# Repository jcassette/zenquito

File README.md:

# Zenquito

Design by J.M. Plantefeve
http://jm.plantefeve.pagesperso-orange.fr

## Class B

R10 = R11 = 68 Ohm

| VDC (V) | Power (W) | Q5       | Q6       | Q7       | Q8       |
| ------- | --------- | -------- | -------- | -------- | -------- |
| 21      | 16        | 2SK1058  | 2SJ162   | none     | none     |
| 25      | 25        | 2SK1058  | 2SJ162   | none     | none     |
| 30      | 40        | 2SK1058  | 2SJ162   | none     | none     |
| 34      | 50        | 2SK1058  | 2SJ162   | 2SK1058  | 2SJ162   |
| 42      | 80        | 2SK1058  | 2SJ162   | 2SK1058  | 2SJ162   |

## Class A

R10 = R11 = 150 Ohm

| VDC (V) | Power (W) | Q5       | Q6       | Q7       | Q8       |
| ------- | --------- | -------- | -------- | -------- | -------- |
| 21      | 16        | 2SK1058  | 2SJ162   | none     | none     |
| 25      | 25        | 2SK1058  | 2SJ162   | 2SK1058  | 2SJ162   |
| 30      | 40        | BUZ900DP | BUZ905DP | BUZ900DP | BUZ905DP |
| 34      | 50        | BUZ900DP | BUZ905DP | BUZ900DP | BUZ905DP |

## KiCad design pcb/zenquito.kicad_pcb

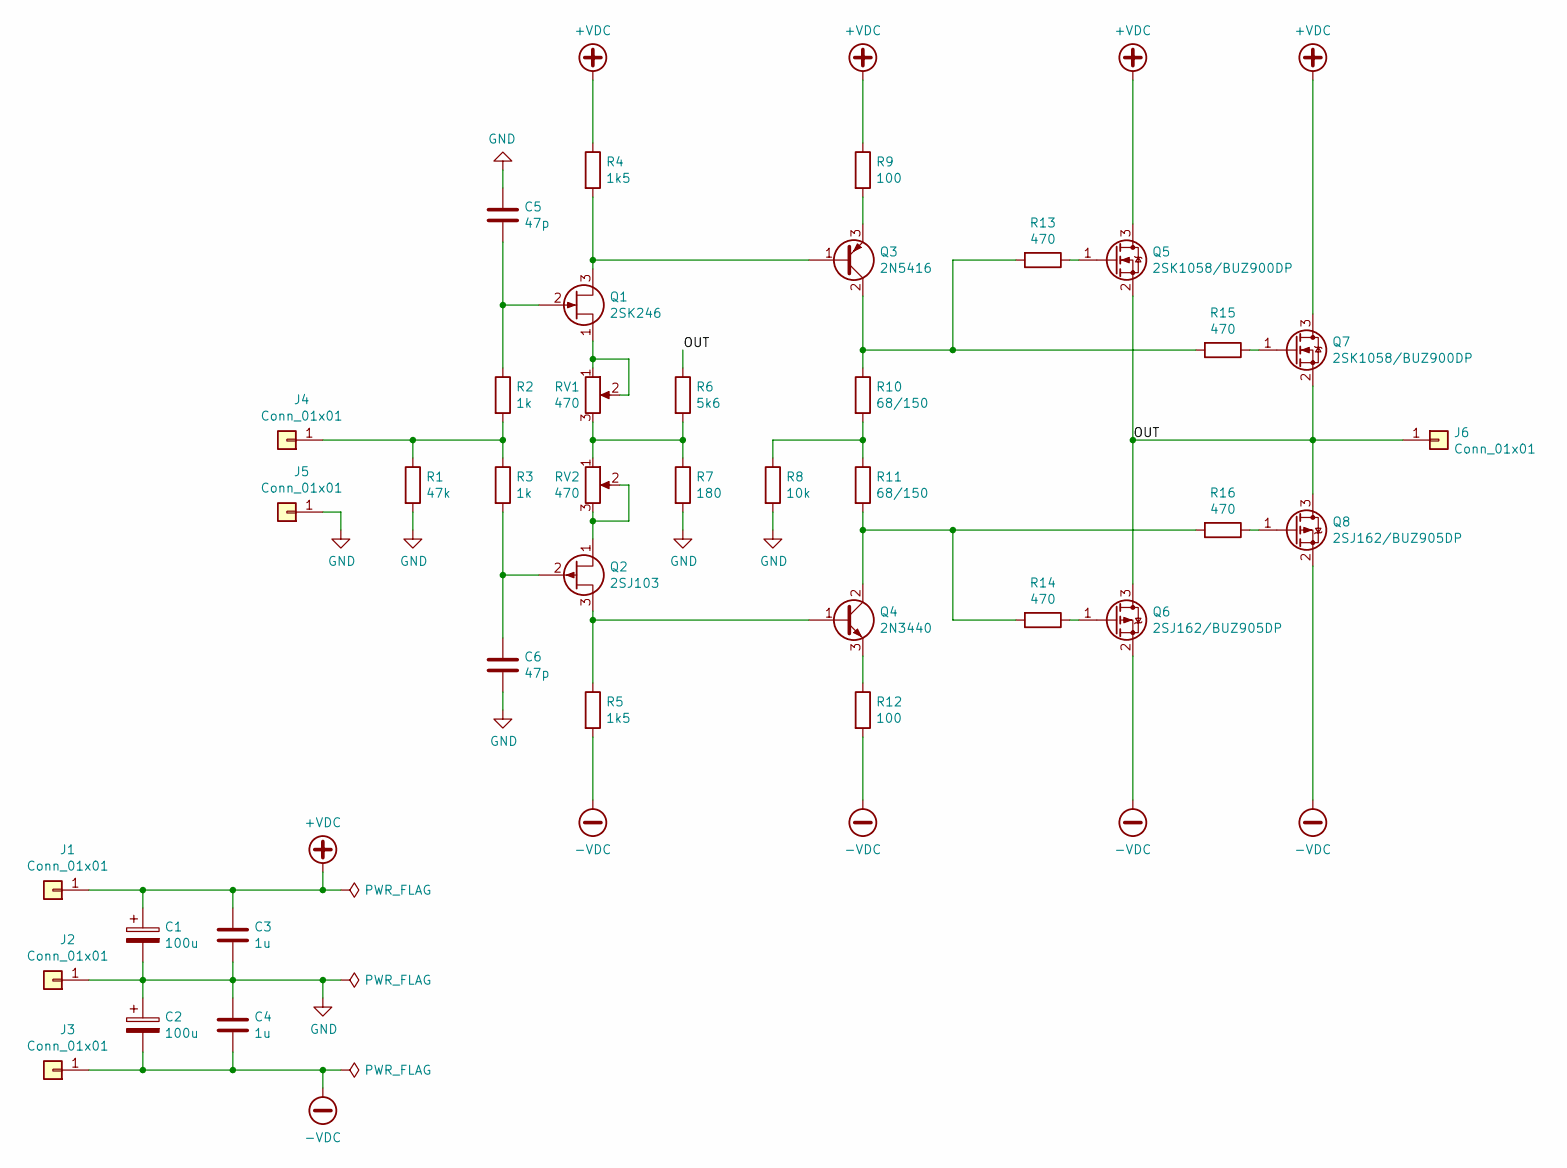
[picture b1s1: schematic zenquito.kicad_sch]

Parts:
C1, C2: 100u; CP_Radial_D8.0mm_P5.00mm
C3, C4: 1u; C_Rect_L7.0mm_W3.5mm_P5.00mm
C5, C6: 47p; C_Rect_L7.0mm_W3.5mm_P5.00mm
J1, J2, J3, J6: Conn_01x01; SolderWire-2.5sqmm_1x01_D2.4mm_OD4.4mm
J4, J5: Conn_01x01; SolderWire-0.5sqmm_1x01_D0.9mm_OD2.1mm
Q1: 2SK246; TO-92_Inline_Wide
Q2: 2SJ103; TO-92_Inline_Wide
Q3: 2N5416; TO-39-3
Q4: 2N3440; TO-39-3
Q5, Q7: 2SK1058/BUZ900DP; TO-3P-3_Vertical
Q6, Q8: 2SJ162/BUZ905DP; TO-3P-3_Vertical
R1: 47k; R_Axial_DIN0411_L9.9mm_D3.6mm_P12.70mm_Horizontal
R2, R3: 1k; R_Axial_DIN0411_L9.9mm_D3.6mm_P12.70mm_Horizontal
R4, R5: 1k5; R_Axial_DIN0411_L9.9mm_D3.6mm_P12.70mm_Horizontal
R6: 5k6; R_Axial_DIN0411_L9.9mm_D3.6mm_P12.70mm_Horizontal
R7: 180; R_Axial_DIN0411_L9.9mm_D3.6mm_P12.70mm_Horizontal
R8: 10k; R_Axial_DIN0411_L9.9mm_D3.6mm_P12.70mm_Horizontal
R9, R12: 100; R_Axial_DIN0411_L9.9mm_D3.6mm_P12.70mm_Horizontal
R10, R11: 68/150; R_Axial_DIN0411_L9.9mm_D3.6mm_P12.70mm_Horizontal
R13, R14, R15, R16: 470; R_Axial_DIN0411_L9.9mm_D3.6mm_P12.70mm_Horizontal
RV1, RV2: 470; Potentiometer_Bourns_3266Y_Vertical

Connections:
+VDC: C1.1, C3.1, J1.1, Q5.3 (D), Q7.3 (D), R4.1, R9.1
-VDC: C2.2, C4.2, J3.1, Q6.2 (S), Q8.2 (S), R5.2, R12.2
/OUT: J6.1, Q5.2 (S), Q6.3 (D), Q7.2 (S), Q8.3 (D), R6.1
GND: C1.2, C2.1, C3.2, C4.1, C5.1, C6.2, J2.1, J5.1, R1.2, R7.2, R8.2
unnamed: C5.2, Q1.2 (G), R2.1
unnamed: C6.1, Q2.2 (G), R3.2
unnamed: J4.1, R1.1, R2.2, R3.1
unnamed: Q1.1 (S), RV1.1, RV1.2
unnamed: Q1.3 (D), Q3.1 (B), R4.2
unnamed: Q2.1 (S), RV2.2, RV2.3
unnamed: Q2.3 (D), Q4.1 (B), R5.1
unnamed: Q3.2 (C), R10.1, R13.2, R15.2
unnamed: Q3.3 (E), R9.2
unnamed: Q4.2 (C), R11.2, R14.2, R16.2
unnamed: Q4.3 (E), R12.1
unnamed: Q5.1 (G), R13.1
unnamed: Q6.1 (G), R14.1
unnamed: Q7.1 (G), R15.1
unnamed: Q8.1 (G), R16.1
unnamed: R6.2, R7.1, RV1.3, RV2.1
unnamed: R8.1, R10.2, R11.1

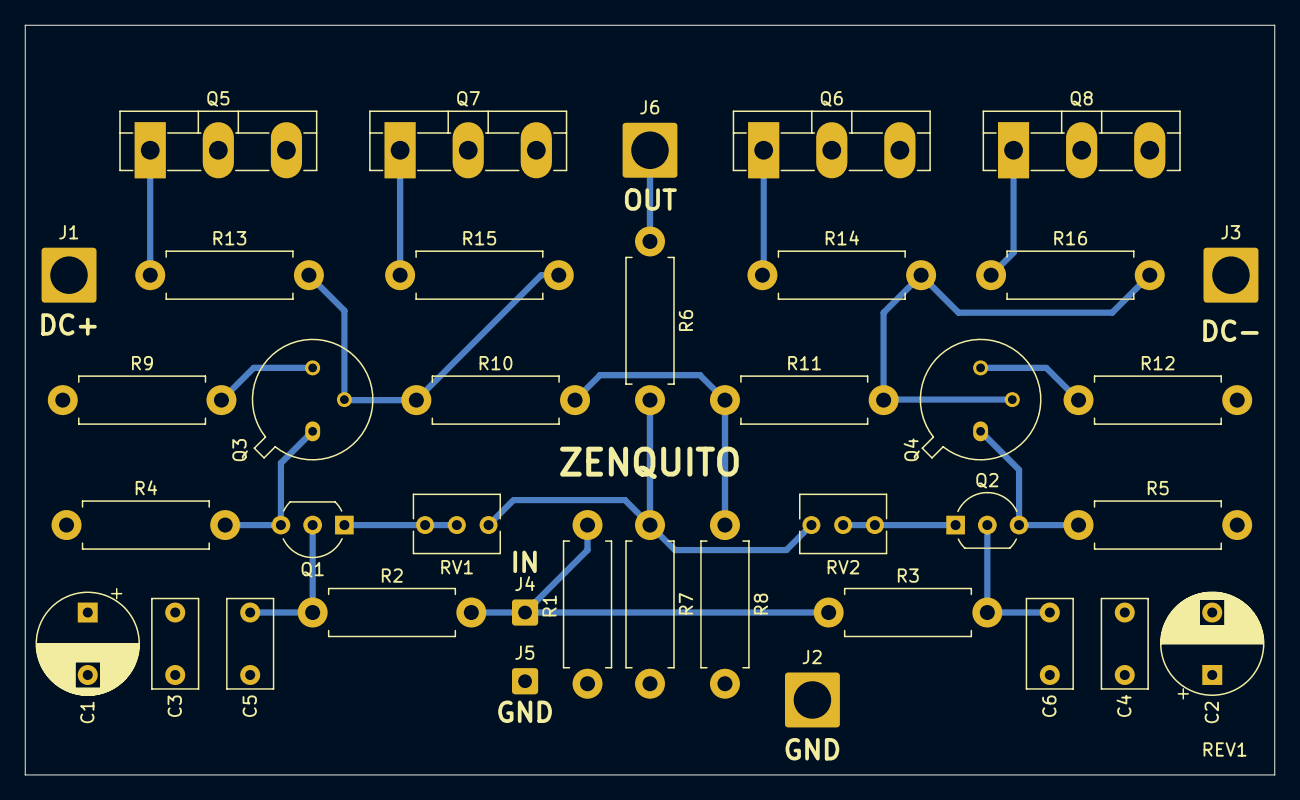
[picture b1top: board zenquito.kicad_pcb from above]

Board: 2 copper layers, 100.0 x 60.0 mm, 38 parts (0 on the bottom side), 21 nets.

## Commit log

2022-01-15 Root commit
2022-01-15 Add some doc
2022-01-15 Add .gitignore
2022-01-15 Revision 1
2022-01-15 Add README.md
